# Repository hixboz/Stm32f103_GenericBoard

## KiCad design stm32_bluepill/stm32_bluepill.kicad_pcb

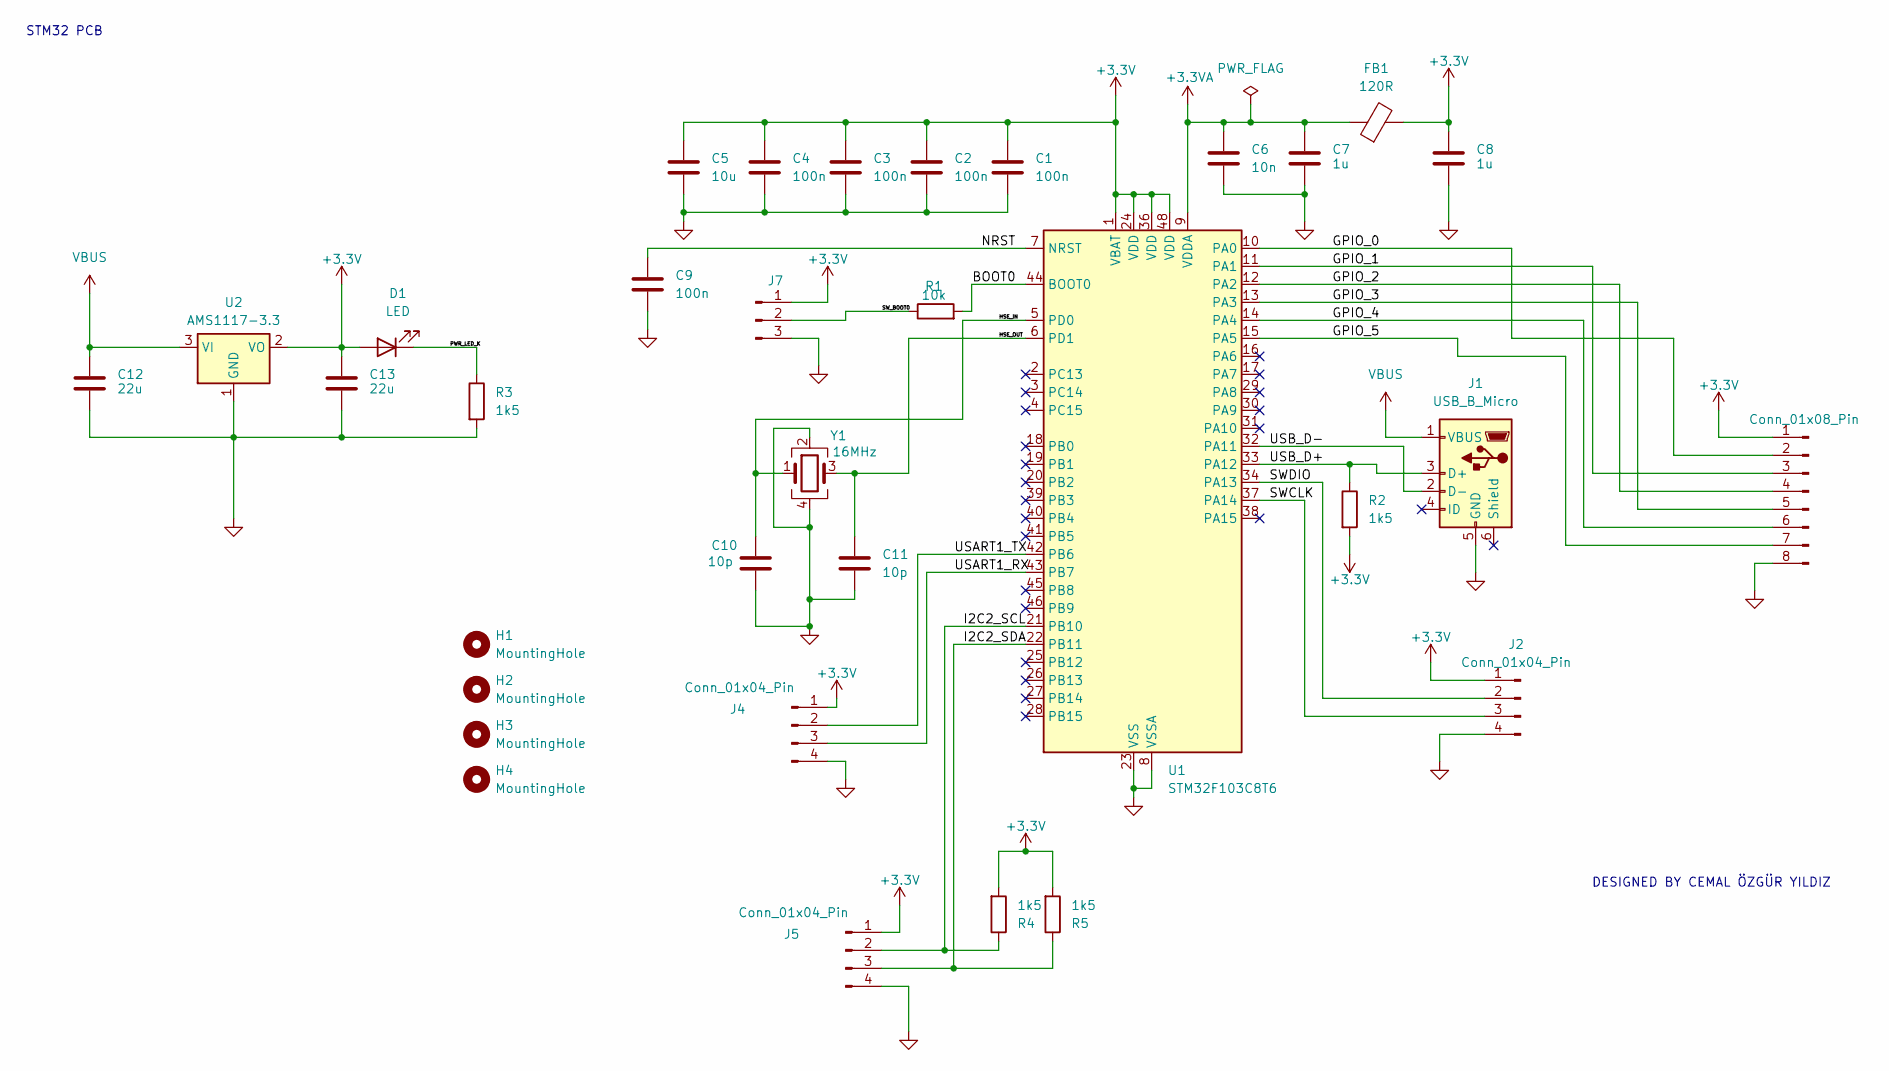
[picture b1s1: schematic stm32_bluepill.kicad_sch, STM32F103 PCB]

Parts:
C1, C2, C3, C4, C9: 100n; C_0402_1005Metric
C5: 10u; C_0603_1608Metric
C6: 10n; C_0402_1005Metric
C7, C8: 1u; C_0402_1005Metric
C10, C11: 10p; C_0402_1005Metric
C12, C13: 22u; C_0805_2012Metric
D1: LED; LED_0603_1608Metric
FB1: 120R; L_0603_1608Metric
H1, H2, H3, H4: MountingHole; MountingHole_2.2mm_M2
J1: USB_B_Micro; USB_Micro-B_Wuerth_629105150521
J2, J4, J5: Conn_01x04_Pin; PinHeader_1x04_P2.54mm_Vertical
J6: Conn_01x08_Pin; PinHeader_1x08_P2.54mm_Vertical
J7: Conn_01x03_Pin; PinHeader_1x03_P2.54mm_Vertical
R1: 10k; R_0402_1005Metric
R2, R3, R4, R5: 1k5; R_0402_1005Metric
U1: STM32F103C8T6; LQFP-48_7x7mm_P0.5mm
U2: AMS1117-3.3; SOT-223-3_TabPin2
Y1: 16MHz; Crystal_SMD_3225-4Pin_3.2x2.5mm_HandSoldering

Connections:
+3.3V: C1.1, C2.1, C3.1, C4.1, C5.1, C8.1, C13.1, D1.2 (A), FB1.2, J2.1, J4.1, J5.1, J6.1, J7.1, R2.2, R4.2, R5.2, U1.1 (VBAT), U1.24 (VDD), U1.36 (VDD), U1.48 (VDD), U2.2 (VO)
+3.3VA: C6.1, C7.1, FB1.1, U1.9 (VDDA)
/BOOT0: R1.2, U1.44 (BOOT0)
/GPIO_0: J6.2, U1.10 (PA0)
/GPIO_1: J6.3, U1.11 (PA1)
/GPIO_2: J6.4, U1.12 (PA2)
/GPIO_3: J6.5, U1.13 (PA3)
/GPIO_4: J6.6, U1.14 (PA4)
/GPIO_5: J6.7, U1.15 (PA5)
/HSE_IN: C10.1, U1.5 (PD0), Y1.1
/HSE_OUT: C11.1, U1.6 (PD1), Y1.3
/I2C2_SCL: J5.2, R4.1, U1.21 (PB10)
/I2C2_SDA: J5.3, R5.1, U1.22 (PB11)
/NRST: C9.1, U1.7 (NRST)
/PWR_LED_K: D1.1 (K), R3.1
/SWCLK: J2.3, U1.37 (PA14)
/SWDIO: J2.2, U1.34 (PA13)
/SW_BOOT0: J7.2, R1.1
/USART1_RX: J4.3, U1.43 (PB7)
/USART1_TX: J4.2, U1.42 (PB6)
/USB_D+: J1.3 (D+), R2.1, U1.33 (PA12)
/USB_D-: J1.2 (D-), U1.32 (PA11)
GND: C1.2, C2.2, C3.2, C4.2, C5.2, C6.2, C7.2, C8.2, C9.2, C10.2, C11.2, C12.2, C13.2, J1.5 (GND), J2.4, J4.4, J5.4, J6.8, J7.3, R3.2, U1.8 (VSSA), U1.23 (VSS), U1.35 (VSS), U1.47 (VSS), U2.1 (GND), Y1.2, Y1.4
VBUS: C12.1, J1.1 (VBUS), U2.3 (VI)

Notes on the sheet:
DESIGNED BY CEMAL ÖZGÜR YILDIZ
STM32 PCB

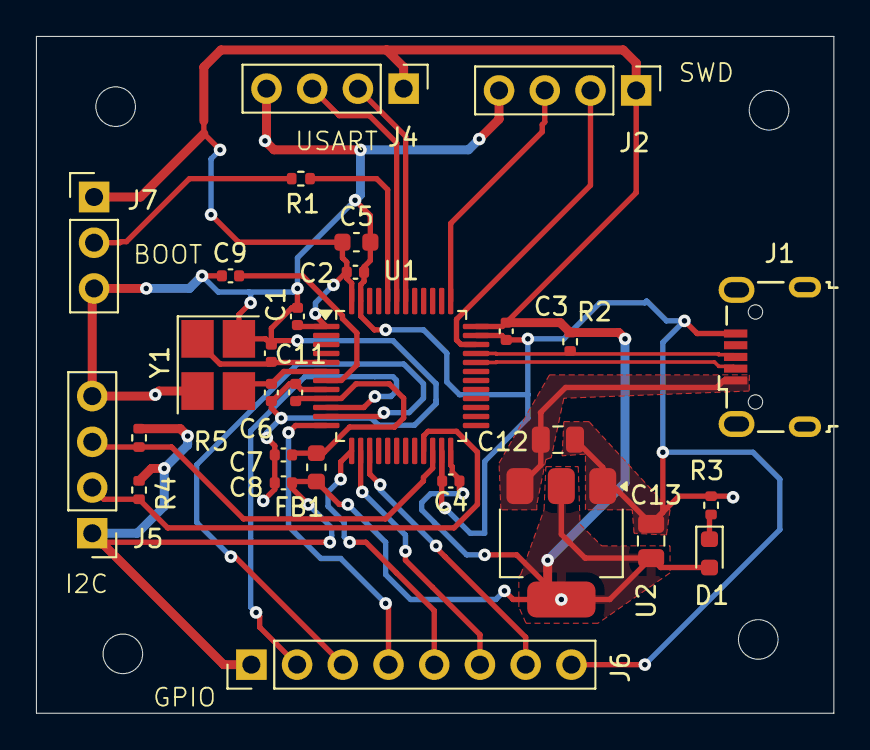
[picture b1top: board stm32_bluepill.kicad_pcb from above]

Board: 2 copper layers, 44.3 x 37.6 mm, 33 parts (0 on the bottom side), 24 nets.

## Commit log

2024-04-01 Scheamtic has added
2024-04-01 Schematic updated
2024-04-03 PCB components located
